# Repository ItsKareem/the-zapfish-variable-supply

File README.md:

# the-zapfish-variable-supply
An AC-to-DC Variable Power Supply (3V–12V)

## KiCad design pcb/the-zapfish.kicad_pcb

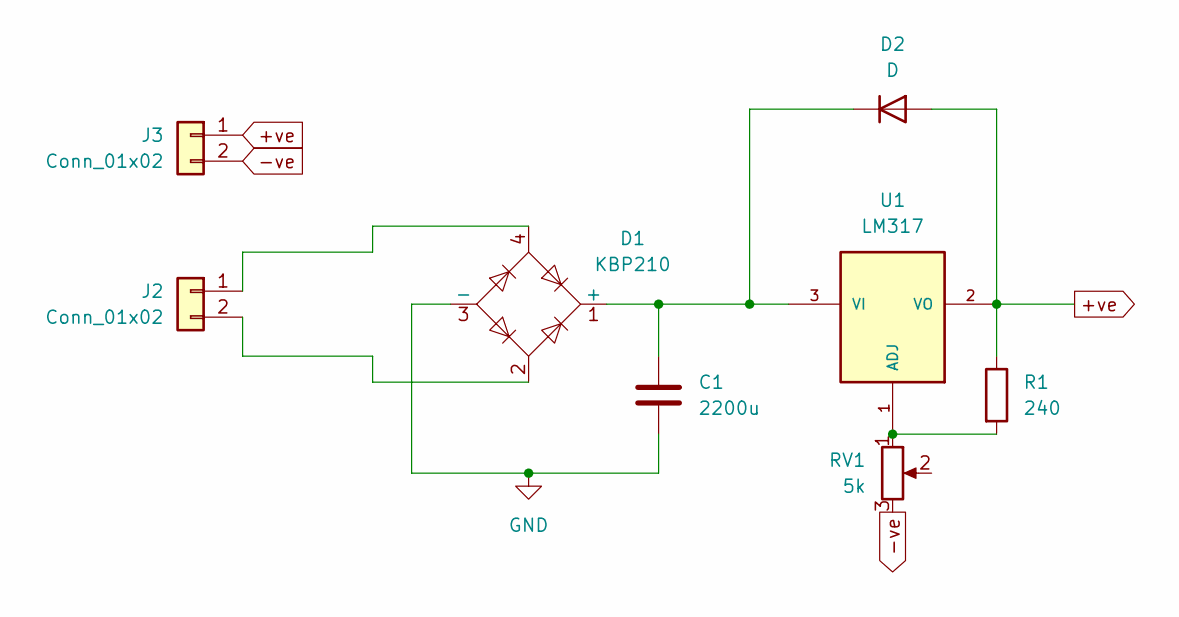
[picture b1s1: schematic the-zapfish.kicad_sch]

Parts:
C1: 2200u; CP_Radial_D12.5mm_P5.00mm
D1: KBP210; SIP380W81P386L1470H1270Q4
D2: D; D_DO-41_SOD81_P10.16mm_Horizontal
J2: Conn_01x02; TerminalBlock_Phoenix_PT-1,5-2-5.0-H_1x02_P5.00mm_Horizontal
J3: Conn_01x02; PinHeader_1x02_P2.54mm_Vertical
R1: 240; R_Axial_DIN0207_L6.3mm_D2.5mm_P2.54mm_Vertical
RV1: 5k; Potentiometer_Vishay_T93YA_Vertical
U1: LM317; TO-220

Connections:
+ve: D2.2 (A), J3.1, R1.1, U1.2 (VO)
-ve: J3.2, RV1.3
GND: C1.2, D1.3 (-)
unnamed: C1.1, D1.1 (+), D2.1 (K), U1.3 (VI)
unnamed: D1.4, J2.1
unnamed: D1.2, J2.2
unnamed: R1.2, RV1.1, U1.1 (ADJ)

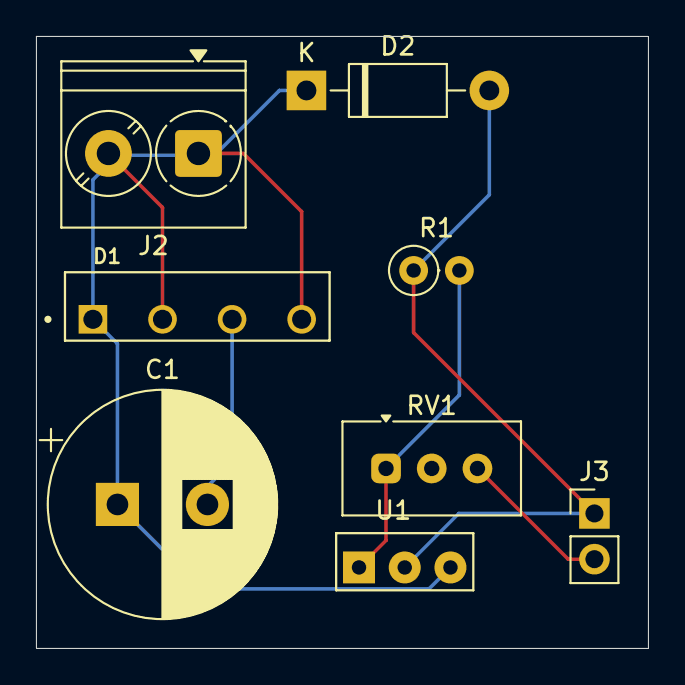
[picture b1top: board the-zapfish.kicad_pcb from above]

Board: 2 copper layers, 34.0 x 34.0 mm, 8 parts (0 on the bottom side), 7 nets.

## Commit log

2026-06-20 Added Files
2026-06-20 Zine page added!
2026-06-20 edit
2026-06-20 README done
2026-06-21 added total
2026-06-23 Adding the zine page as an image
2026-06-23 Add zine page to README
